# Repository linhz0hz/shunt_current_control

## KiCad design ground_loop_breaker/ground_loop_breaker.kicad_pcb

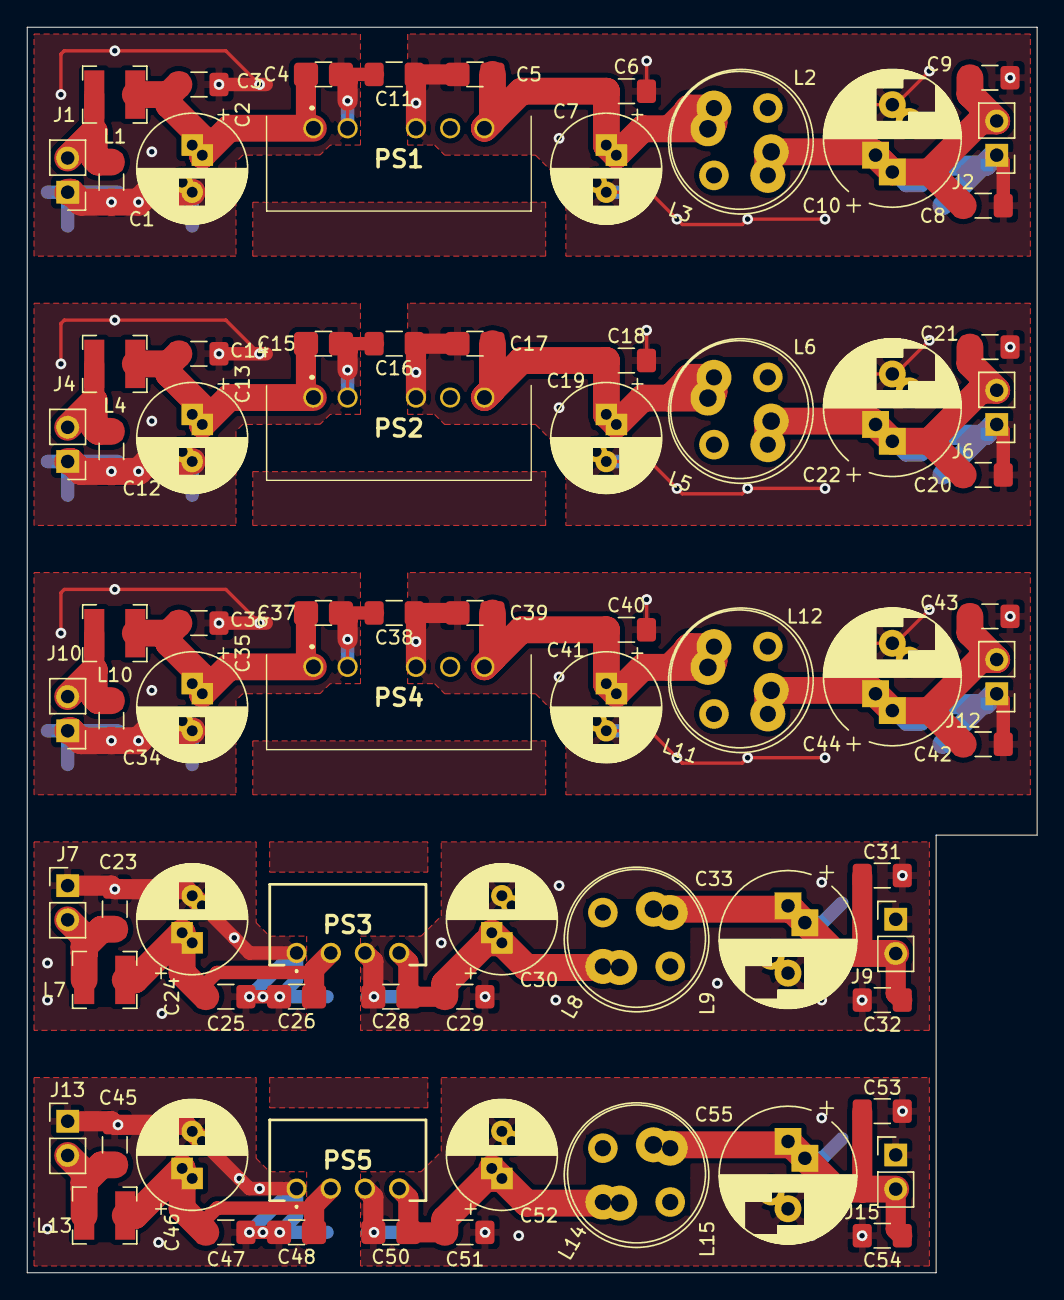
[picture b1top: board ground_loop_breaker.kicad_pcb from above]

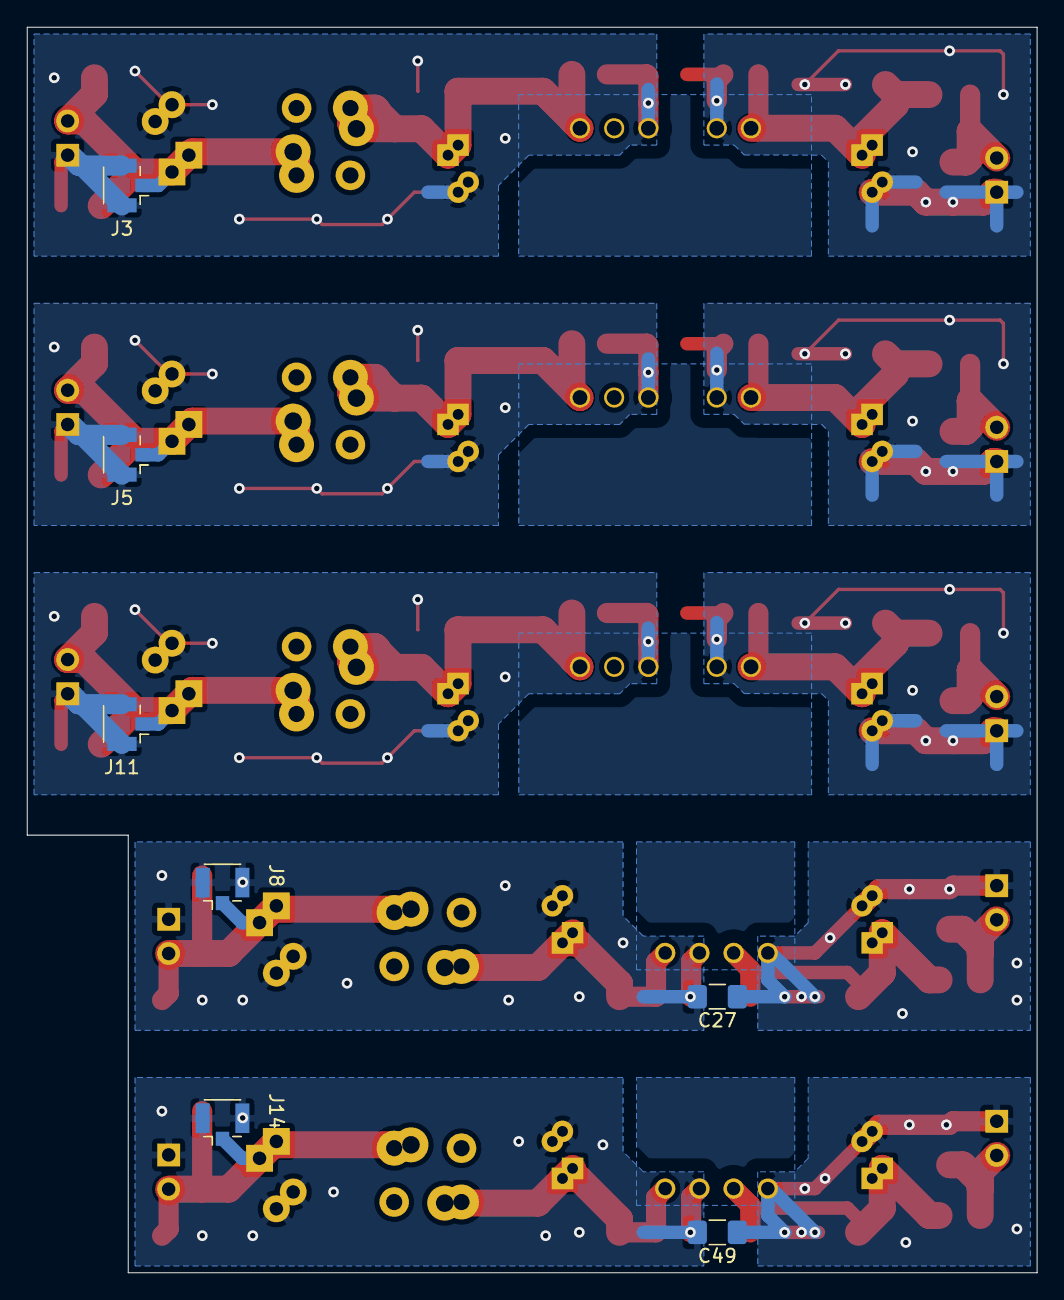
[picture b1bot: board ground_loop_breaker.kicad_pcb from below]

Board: 2 copper layers, 75.0 x 92.5 mm, 90 parts (7 on the bottom side), 30 nets.

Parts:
C1, C3, C6, C8, C9, C12, C14, C18, C20, C21, C23, C25, C29, C31, C32, C34, C36, C40, C42, C43, C45, C47, C51, C53, C54: C; C_1206_3216Metric_Pad1.42x1.75mm_HandSolder
C2, C7, C13, C19, C24, C30, C35, C41, C46, C52: CP; CP_Radial_D8_P3.5_2.5
C4, C5, C15, C17, C26, C28, C37, C39, C48, C50: C; C_1206_0805_dual
C10, C22, C33, C44, C55: CP; CP_Radial_D10.0mm_P3.5_5
C11, C16, C27, C38, C49: 270p 1kV; C_1206_3216Metric_Pad1.42x1.75mm_HandSolder
J1, J2, J4, J6, J7, J9, J10, J12, J13, J15: Conn_01x02_Male; PinHeader_1x02_P2.54mm_Vertical
J3, J5, J8, J11, J14: Conn_Coaxial; U.FL_Hirose_U.FL-R-SMT-1_Vertical
L1, L4, L7, L10, L13: L; L_Bourns-SRN4018
L2, L6, L9, L12, L15: 12RS105C; L_Radial_D10.5mm_P4.00x5.00mm_Murata_1200RS
L3, L5, L8, L11, L14: 12RS105C; L_Radial_D10.0mm_P5.00mm_Fastron_07P
PS1, PS2, PS4: PDM2-S5-S5-S; PDM2S5S5S
PS3, PS5: PDSE1-S5-S5-S; PDSE1S5S5S

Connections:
/power_module_A/VinN: C1.2, C2.2, C3.2, C4.2, C11.2, J1.1, PS1.2
/power_module_A/VinP: C1.1, J1.2, L1.1
/power_module_A/VoutN: C5.2, C6.2, C7.2, C8.2, C9.2, C10.2, C11.1, J2.1, J3.2, PS1.4
/power_module_A/VoutP: C8.1, C9.1, C10.1, J2.2, J3.1, L2.1, L3.1
/power_module_D/VinN: C23.2, C24.2, C25.2, C26.2, C27.2, J7.1, PS3.1
/power_module_D/VinP: C23.1, J7.2, L7.1
/power_module_D/VoutN: C27.1, C28.2, C29.2, C30.2, C31.2, C32.2, C33.2, J8.2, J9.1, PS3.3
/power_module_D/VoutP: C31.1, C32.1, C33.1, J8.1, J9.2, L8.1, L9.1
/sheet61365BC2/VinN: C45.2, C46.2, C47.2, C48.2, C49.2, J13.1, PS5.1
/sheet61365BC2/VinP: C45.1, J13.2, L13.1
/sheet61365BC2/VoutN: C49.1, C50.2, C51.2, C52.2, C53.2, C54.2, C55.2, J14.2, J15.1, PS5.3
/sheet61365BC2/VoutP: C53.1, C54.1, C55.1, J14.1, J15.2, L14.1, L15.1
/sheet613586DC/VinN: C12.2, C13.2, C14.2, C15.2, C16.2, J4.1, PS2.2
/sheet613586DC/VinP: C12.1, J4.2, L4.1
/sheet613586DC/VoutN: C16.1, C17.2, C18.2, C19.2, C20.2, C21.2, C22.2, J5.2, J6.1, PS2.4
/sheet613586DC/VoutP: C20.1, C21.1, C22.1, J5.1, J6.2, L5.1, L6.1
/sheet61358710/VinN: C34.2, C35.2, C36.2, C37.2, C38.2, J10.1, PS4.2
/sheet61358710/VinP: C34.1, J10.2, L10.1
/sheet61358710/VoutN: C38.1, C39.2, C40.2, C41.2, C42.2, C43.2, C44.2, J11.2, J12.1, PS4.4
/sheet61358710/VoutP: C42.1, C43.1, C44.1, J11.1, J12.2, L11.1, L12.1
unnamed: C2.1, C3.1, C4.1, L1.2, PS1.1
unnamed: C5.1, C6.1, C7.1, L2.2, L3.2, PS1.6
unnamed: C13.1, C14.1, C15.1, L4.2, PS2.1
unnamed: C17.1, C18.1, C19.1, L5.2, L6.2, PS2.6
unnamed: C24.1, C25.1, C26.1, L7.2, PS3.2
unnamed: C28.1, C29.1, C30.1, L8.2, L9.2, PS3.4
unnamed: C35.1, C36.1, C37.1, L10.2, PS4.1
unnamed: C39.1, C40.1, C41.1, L11.2, L12.2, PS4.6
unnamed: C46.1, C47.1, C48.1, L13.2, PS5.2
unnamed: C50.1, C51.1, C52.1, L14.2, L15.2, PS5.4

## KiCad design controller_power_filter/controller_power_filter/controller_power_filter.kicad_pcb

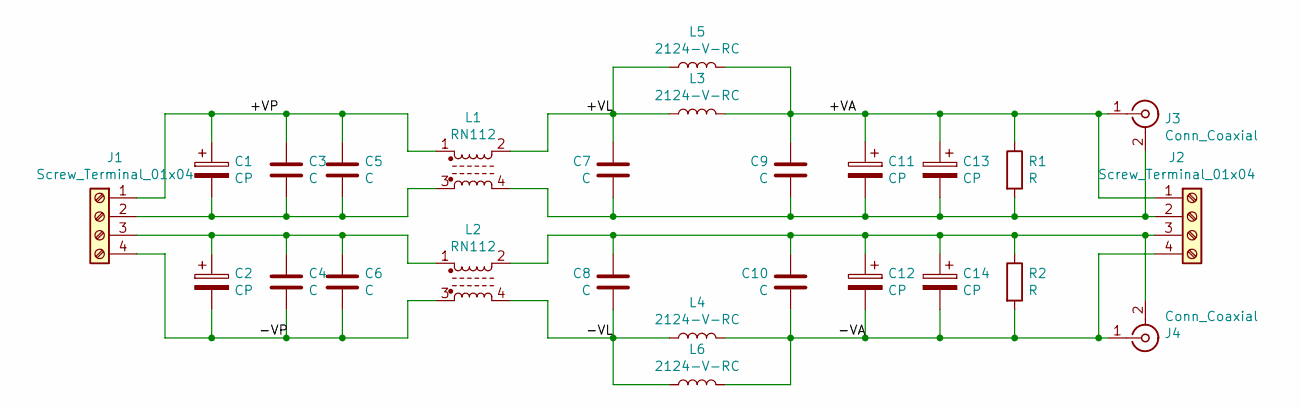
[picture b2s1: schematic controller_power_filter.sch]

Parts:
C1, C2, C11, C12, C13, C14: CP; CP_Radial_D10.0mm_P3.5_5
C3, C4, C5, C6, C7, C8, C9, C10: C; C_1206_0805_dual
J1, J2: Screw_Terminal_01x04; TerminalBlock_bornier-4_P5.08mm
J3, J4: Conn_Coaxial; U.FL_Hirose_U.FL-R-SMT-1_Vertical
L1, L2: RN112; Choke_Schaffner_RN102_112_204
L3, L4: 2124-V-RC; L_Toroid_Vertical_L21.6mm_W11.4mm_P7.62mm_Pulse_KM-3
L5, L6: 2124-V-RC; L_10.4x10.4_H4.8
R1, R2: R; R_1206_0805_dual

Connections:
/+VA: C9.1, C11.1, C13.1, J2.1, J3.1 (In), L3.2, L5.2, R1.1
/+VL: C7.1, L1.2, L3.1, L5.1
/+VP: C1.1, C3.1, C5.1, J1.1, L1.1
/-VA: C10.2, C12.2, C14.2, J2.4, J4.1 (In), L4.2, L6.2, R2.2
/-VL: C8.2, L2.4, L4.1, L6.1
/-VP: C2.2, C4.2, C6.2, J1.4, L2.3
unnamed: C1.2, C3.2, C5.2, J1.2, L1.3
unnamed: C2.1, C4.1, C6.1, J1.3, L2.1
unnamed: C8.1, C10.1, C12.1, C14.1, J2.3, J4.2 (Ext), L2.2, R2.1
unnamed: C7.2, C9.2, C11.2, C13.2, J2.2, J3.2 (Ext), L1.4, R1.2

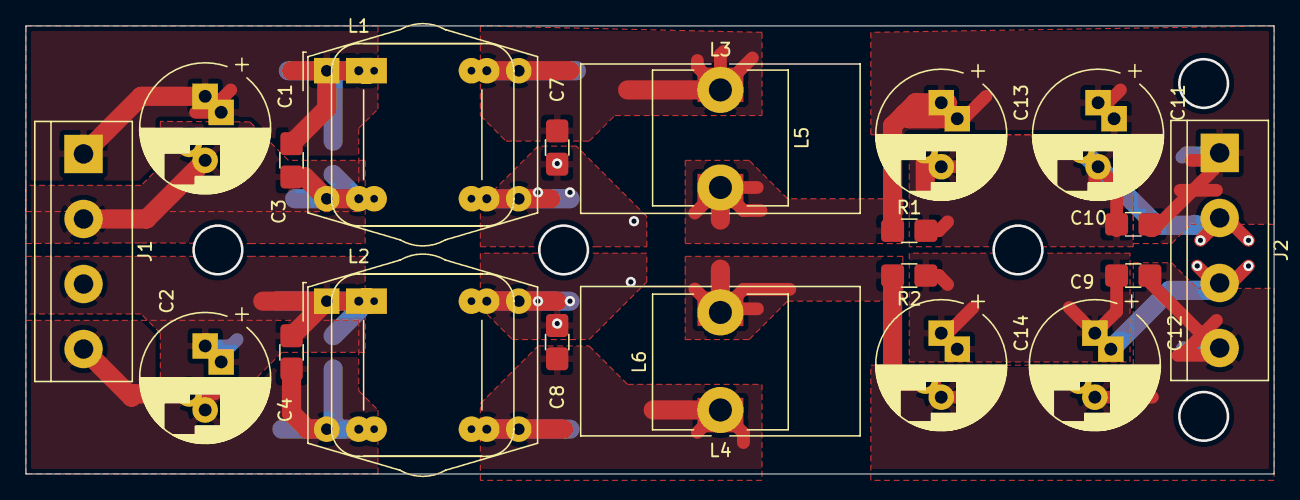
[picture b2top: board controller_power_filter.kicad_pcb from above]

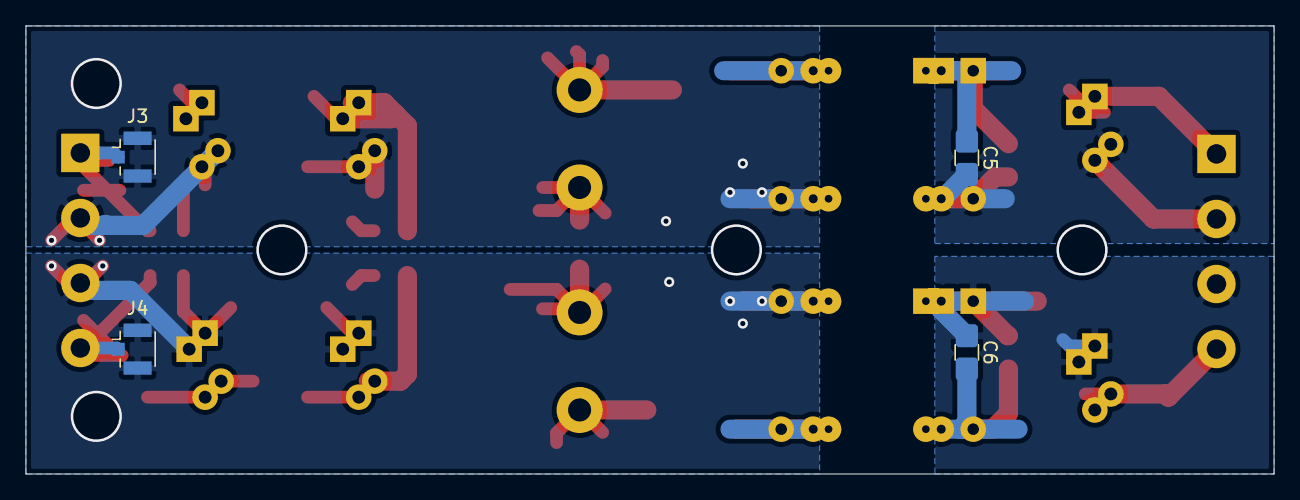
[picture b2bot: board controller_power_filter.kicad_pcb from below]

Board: 2 copper layers, 97.5 x 35.0 mm, 26 parts (4 on the bottom side), 10 nets.

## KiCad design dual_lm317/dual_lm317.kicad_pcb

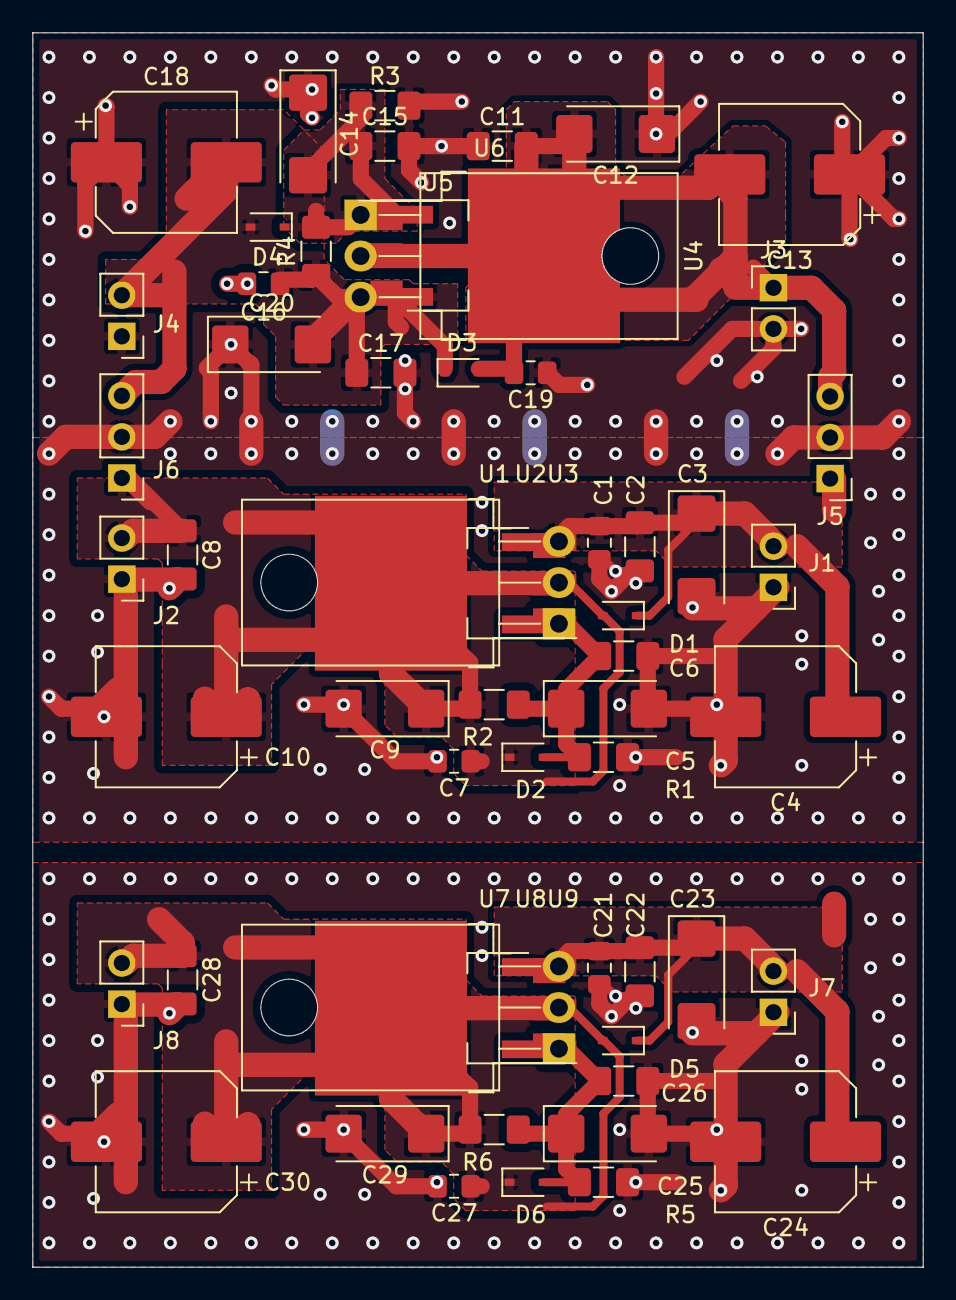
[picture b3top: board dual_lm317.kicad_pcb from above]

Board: 2 copper layers, 55.0 x 76.2 mm, 59 parts (0 on the bottom side), 11 nets.

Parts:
C1, C7, C16, C19, C21, C27: 0.1u; C_0805_2012Metric_Pad1.15x1.40mm_HandSolder
C2, C8, C11, C17, C22, C28: 1u; C_1206_3216Metric_Pad1.42x1.75mm_HandSolder
C3, C5, C9, C12, C14, C20, C23, C25, C29: Tant 10uF; CP_EIA-6032-15_Kemet-U_Pad2.25x2.35mm_HandSolder
C4, C10, C13, C18, C24, C30: Electrolytic; CP_Elec_8x10.5
C6, C15, C26: 0.01u c0g; C_1206_3216Metric_Pad1.42x1.75mm_HandSolder
D1, D2, D3, D4, D5, D6: D; D_SOD-323
J1, J2, J3, J4, J7, J8: Conn_01x02_Male; PinHeader_1x02_P2.54mm_Vertical
J5, J6: Conn_01x03_Male; PinHeader_1x03_P2.54mm_Vertical
R1, R2, R3, R4, R5, R6: R; R_1206_3216Metric_Pad1.42x1.75mm_HandSolder
U1, U7: LM317_3PinPackage; TO-220-3_Horizontal_TabDown
U2, U8: LT3080xST; SOT-223
U3, U9: LT3080xST; TO-263-3_TabPin4
U4: LM337_TO220; TO-220-3_Horizontal_TabDown
U5: LM337_SOT223; SOT-223-3_TabPin2
U6: LM337_TO263; TO-263-2

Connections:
/GNDA: C1.2, C2.2, C3.2, C4.2, C5.2, C6.2, C7.2, C8.2, C9.2, C10.2, C11.1, C12.1, C13.1, C14.1, C15.2, C16.2, C17.2, C18.1, C19.1, C20.1, J1.1, J2.1, J3.2, J4.1, J5.2, J6.2, R1.2, R3.2
/GNDB: C21.2, C22.2, C23.2, C24.2, C25.2, C26.2, C27.2, C28.2, C29.2, C30.2, J7.1, J8.1, R5.2
/VadjA: C5.1, C6.1, D2.2, R1.1, R2.2, U1.1, U2.1, U3.1
/VadjAN: C14.2, C15.1, D4.1, R3.1, R4.2, U4.1, U5.1, U6.1
/VadjB: C25.1, C26.1, D6.2, R5.1, R6.2, U7.1, U8.1, U9.1
/VinA: C1.1, C2.1, C3.1, C4.1, D1.1, J1.2, J5.1, U1.3, U2.3, U3.3
/VinAN: C11.2, C12.2, C13.2, C19.2, D3.2, J3.1, J5.3, U4.2, U5.2, U6.2
/VinB: C21.1, C22.1, C23.1, C24.1, D5.1, J7.2, U7.3, U8.3, U9.3
/VoutA: C7.1, C8.1, C9.1, C10.1, D1.2, D2.1, J2.2, J6.1, R2.1, U1.2, U2.2, U2.4, U3.2, U3.4
/VoutAN: C16.1, C17.1, C18.2, C20.2, D3.1, D4.2, J4.2, J6.3, R4.1, U4.3, U5.3, U6.3
/VoutB: C27.1, C28.1, C29.1, C30.1, D5.2, D6.1, J8.2, R6.1, U7.2, U8.2, U8.4, U9.2, U9.4

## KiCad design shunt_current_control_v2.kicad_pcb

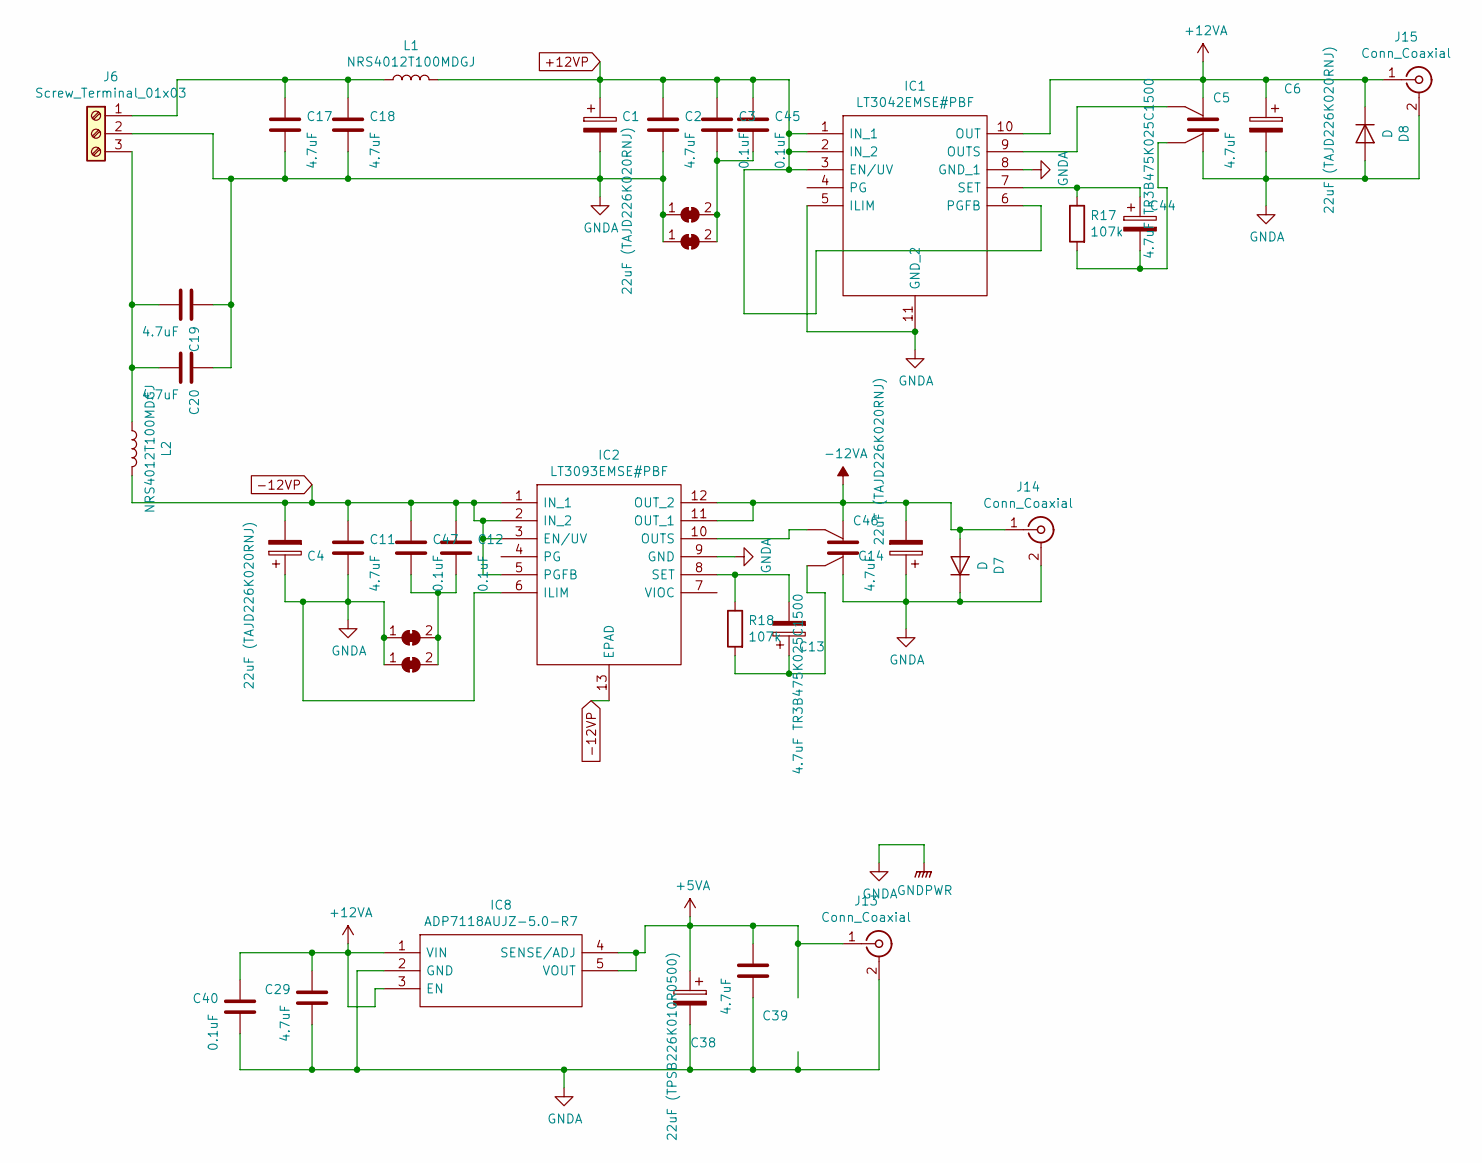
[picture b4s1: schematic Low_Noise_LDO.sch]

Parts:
C1, C4, C6, C14: 22uF (TAJD226K020RNJ); CP_EIA-7343-30_AVX-N_Pad2.25x2.55mm_HandSolder
C2, C11, C17, C18, C19, C20, C29, C39: 4.7uF; C_1206_3216Metric_Pad1.42x1.75mm_HandSolder
C3, C12, C40, C45, C47: 0.1uF; C_0805_2012Metric_Pad1.15x1.40mm_HandSolder
C5, C46: 4.7uF; C_1206_3216Metric_Pad1.42x1.75mm_Kelvin
C13, C44: 4.7uF TR3B475K025C1500; CP_EIA-3528-12_Kemet-T_Pad1.50x2.35mm_HandSolder
C38: 22uF (TPSB226K010R0500); CP_EIA-3528-15_AVX-H_Pad1.50x2.35mm_HandSolder
D7, D8: D; D_SOD-323_HandSoldering
IC1: LT3042EMSE#PBF; SOP50P490X110-11N; Mouser Part Number 584-LT3042EMSE#PBF
IC2: LT3093EMSE#PBF; SOP65P490X110-13N; Mouser Part Number 584-LT3093EMSE#PBF
IC8: ADP7118AUJZ-5.0-R7; SOT95P280X100-5N; Mouser Part Number 584-ADP7118AUJZ5.0R7
J6: Screw_Terminal_01x03; TerminalBlock_bornier-3_P5.08mm
J13, J14, J15: Conn_Coaxial; Coaxial_IPX_TE_23370191-1-2
JP5, JP6, JP7, JP8: SolderJumper_2_Bridged; DummyJumperStub
L1, L2: NRS4012T100MDGJ; L_Taiyo-Yuden_NR-40xx
R17, R18: 107k; R_0805_2012Metric_Pad1.15x1.40mm_HandSolder

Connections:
+5VA: C38.1, C39.1, IC8.4 (SENSE/ADJ), IC8.5 (VOUT), J13.1 (In); also elsewhere on the board
+12VA: C5.1, C6.1, C29.1, C40.1, D8.1 (K), IC1.10 (OUT), IC8.1 (VIN), IC8.3 (EN), J15.1 (In); also elsewhere on the board
+12VP: C1.1, C2.1, C3.1, C45.1, IC1.1 (IN_1), IC1.2 (IN_2), IC1.3 (EN/UV), IC1.6 (PGFB), L1.2; also elsewhere on the board
-12VA: C14.2, C46.1, D7.2 (A), IC2.11 (OUT_1), IC2.12 (OUT_2), J14.1 (In); also elsewhere on the board
-12VP: C4.2, C11.1, C12.1, C47.1, IC2.1 (IN_1), IC2.2 (IN_2), IC2.3 (EN/UV), IC2.5 (PGFB), IC2.13 (EPAD), L2.2
GNDA: C1.2, C2.2, C4.1, C5.2, C6.2, C11.2, C14.1, C17.2, C18.2, C19.1, C20.1, C29.2, C38.2, C39.2, C40.2, C46.2, D7.1 (K), D8.2 (A), IC1.5 (ILIM), IC1.8 (GND_1), IC1.11 (GND_2), IC2.6 (ILIM), IC2.9 (GND), IC8.2 (GND), J6.2, J13.2 (Ext), J14.2 (Ext), J15.2 (Ext), JP5.1 (A), JP6.1 (A), JP7.1 (A), JP8.1 (A); also elsewhere on the board
unnamed: C3.2, C45.2, JP5.2 (B), JP6.2 (B)
unnamed: C5.3, IC1.9 (OUTS)
unnamed: C12.2, C47.2, JP7.2 (B), JP8.2 (B)
unnamed: C13.1, C46.4, R18.2
unnamed: C13.2, IC2.8 (SET), R18.1
unnamed: C17.1, C18.1, J6.1, L1.1
unnamed: C19.2, C20.2, J6.3, L2.1
unnamed: C44.1, IC1.7 (SET), R17.1
unnamed: C5.4, C44.2, R17.2
unnamed: C46.3, IC2.10 (OUTS)

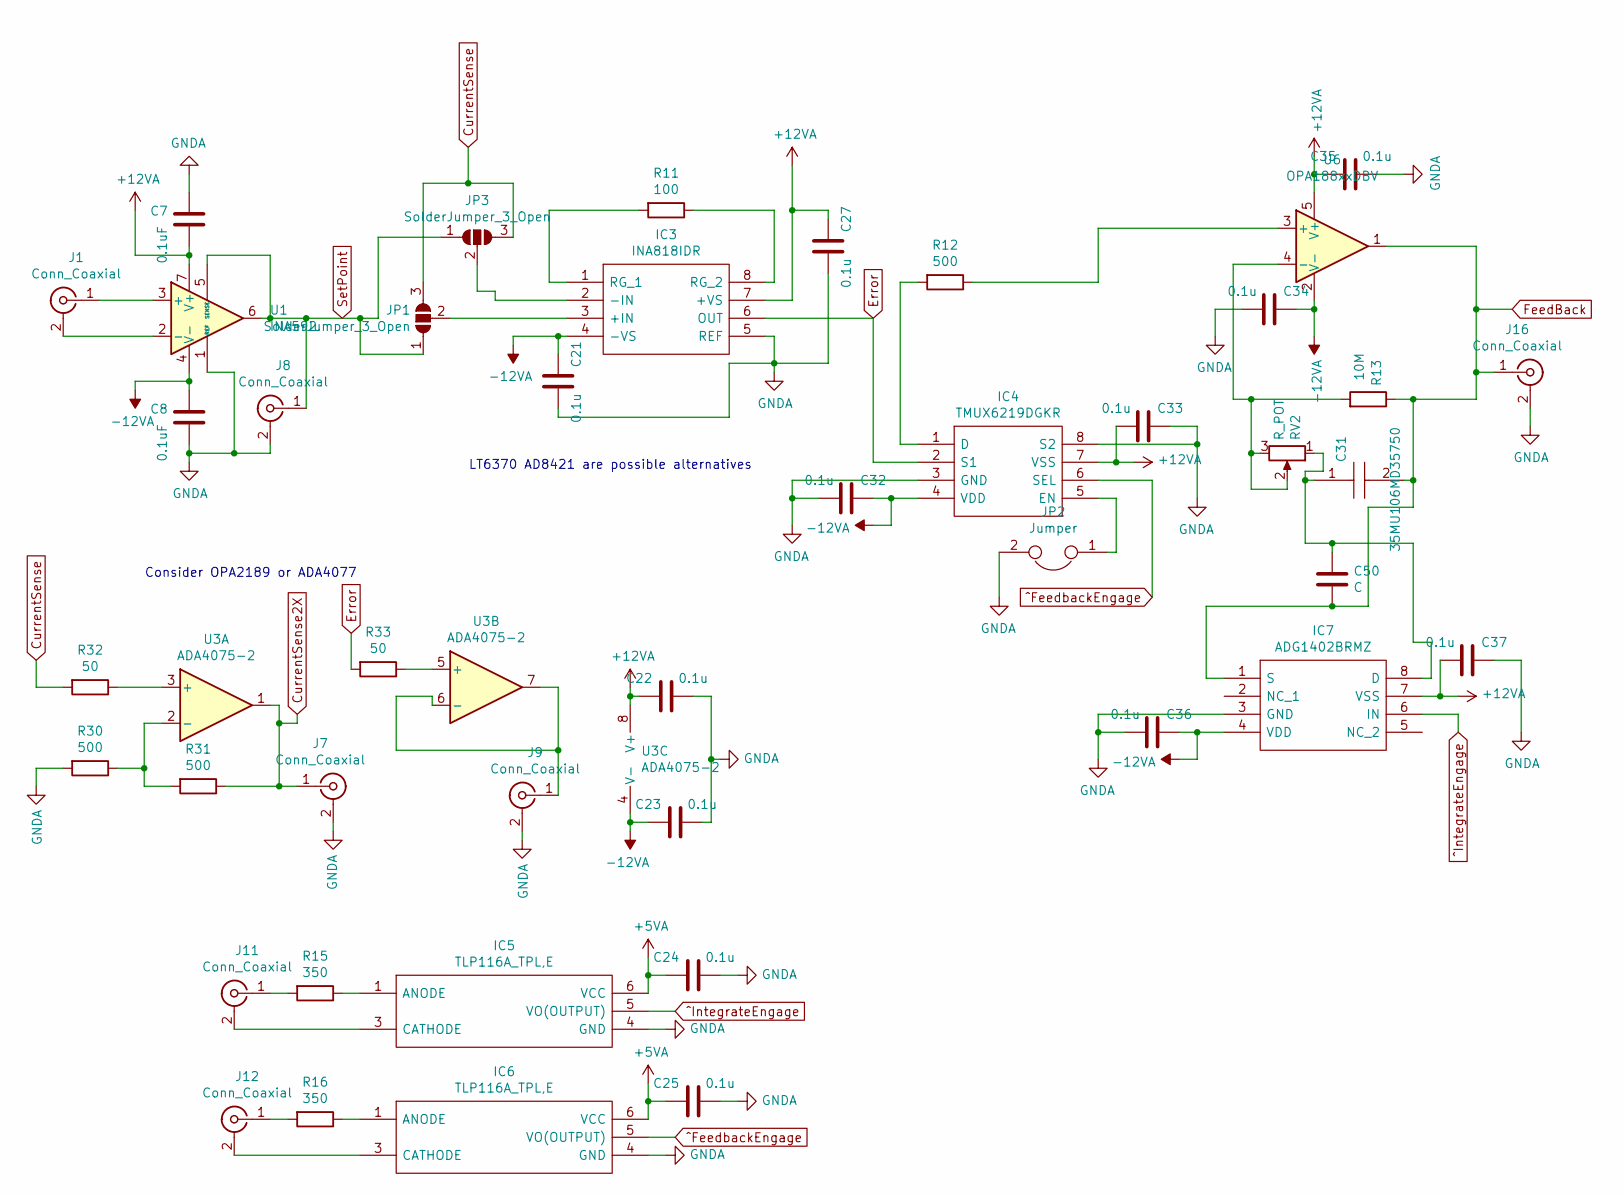
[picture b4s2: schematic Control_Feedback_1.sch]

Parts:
C7, C8: 0.1uF; C_0805_2012Metric_Pad1.15x1.40mm_HandSolder
C21, C22, C23, C24, C25, C27, C32, C33, C34, C35, C36, C37: 0.1u; C_0805_2012Metric_Pad1.15x1.40mm_HandSolder
C31: 35MU106MD35750; CAPC5750X280N; Mouser Part Number 232-35MU106MD35750
C50: C; C_Radial_D8.0mm_H7.0mm_P3.50mm
IC3: INA818IDR; SOIC-8_3.9x4.9mm_P1.27mm; Mouser Part Number 595-INA818IDR
IC4: TMUX6219DGKR; SOP65P490X110-8N; Mouser Part Number 595-TMUX6219DGKR
IC5, IC6: TLP116A_TPL,E; SOT127P700X230-5N; Mouser Part Number 757-TLP116A(TPLE
IC7: ADG1402BRMZ; SOP65P490X110-8N; Mouser Part Number 584-ADG1402BRMZ
J1: Conn_Coaxial; SMA_Amphenol_132134-10_Vertical
J7, J8, J9, J11, J12, J16: Conn_Coaxial; Coaxial_IPX_TE_23370191-1-2
JP1, JP3: SolderJumper_3_Open; SolderJumper-3_P1.3mm_Open_RoundedPad1.0x1.5mm
JP2: Jumper; SolderJumper-2_P1.3mm_Open_RoundedPad1.0x1.5mm
R11: 100; R_1206_3216Metric_Pad1.42x1.75mm_HandSolder
R12: 500; R_1206_3216Metric_Pad1.42x1.75mm_HandSolder
R13: 10M; R_1206_3216Metric_Pad1.42x1.75mm_HandSolder
R15, R16: 350; R_0805_2012Metric_Pad1.15x1.40mm_HandSolder
R30, R31: 500; R_1206_0805_dual
R32, R33: 50; R_0805_2012Metric_Pad1.15x1.40mm_HandSolder
RV2: R_POT; 3361P1253GLF
U1: INA592; SOIC-8_3.9x4.9mm_P1.27mm
U3: ADA4075-2; SOIC-8_3.9x4.9mm_P1.27mm
U6: OPA188xxDBV; TSOT-23-5

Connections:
+5VA: C24.2, C25.2, IC5.6 (VCC), IC6.6 (VCC); also elsewhere on the board
+12VA: C7.2, C22.2, C27.2, C33.1, C35.2, C37.1, IC3.7 (+VS), IC4.7 (VSS), IC7.7 (VSS), U1.7 (V+), U3.8 (V+), U6.5 (V+); also elsewhere on the board
-12VA: C8.1, C21.2, C23.2, C32.2, C34.2, C36.2, IC3.4 (-VS), IC4.4 (VDD), IC7.4 (VDD), U1.4 (V-), U3.4 (V-), U6.2 (V-); also elsewhere on the board
CurrentSense: JP1.3 (B), JP3.3 (B), R32.2; also elsewhere on the board
CurrentSense2X: J7.1 (In), R31.1, U3.1
Error: IC3.6 (OUT), IC4.2 (S1), R33.2
FeedBack: C31.2, C50.1, IC7.1 (S), J16.1 (In), R13.1, U6.1; also elsewhere on the board
GNDA: C7.1, C8.2, C21.1, C22.1, C23.1, C24.1, C25.1, C27.1, C32.1, C33.2, C34.1, C35.1, C36.1, C37.2, IC3.5 (REF), IC4.3 (GND), IC4.8 (S2), IC5.4 (GND), IC6.4 (GND), IC7.3 (GND), J7.2 (Ext), J8.2 (Ext), J9.2 (Ext), J16.2 (Ext), JP2.2, R30.2, U1.1 (REF); also elsewhere on the board
unnamed: C31.1, C50.2, IC7.8 (D), RV2.1
unnamed: IC3.1 (RG_1), R11.2
unnamed: IC3.2 (-IN), JP3.2 (C)
unnamed: IC3.3 (+IN), JP1.2 (C)
unnamed: IC3.8 (RG_2), R11.1
unnamed: IC4.1 (D), R12.2
unnamed: IC4.5 (EN), JP2.1
unnamed: IC5.1 (ANODE), R15.1
unnamed: IC5.3 (CATHODE), J11.2 (Ext)
unnamed: IC6.1 (ANODE), R16.1
unnamed: IC6.3 (CATHODE), J12.2 (Ext)
unnamed: J1.1 (In), U1.3 (+)
unnamed: J1.2 (Ext), U1.2 (-)
unnamed: J9.1 (In), U3.6 (-), U3.7
unnamed: J11.1 (In), R15.2
unnamed: J12.1 (In), R16.2
unnamed: R12.1, U6.3 (+)
unnamed: R13.2, RV2.2, RV2.3, U6.4 (-)
unnamed: R30.1, R31.2, U3.2 (-)
unnamed: R32.1, U3.3 (+)
unnamed: R33.1, U3.5 (+)
SetPoint: J8.1 (In), JP1.1 (A), JP3.1 (A), U1.5 (SENSE), U1.6
^FeedbackEngage: IC4.6 (SEL), IC6.5 (VO(OUTPUT))
^IntegrateEngage: IC5.5 (VO(OUTPUT)), IC7.6 (IN)

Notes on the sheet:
Consider OPA2189 or ADA4077
LT6370 AD8421 are possible alternatives

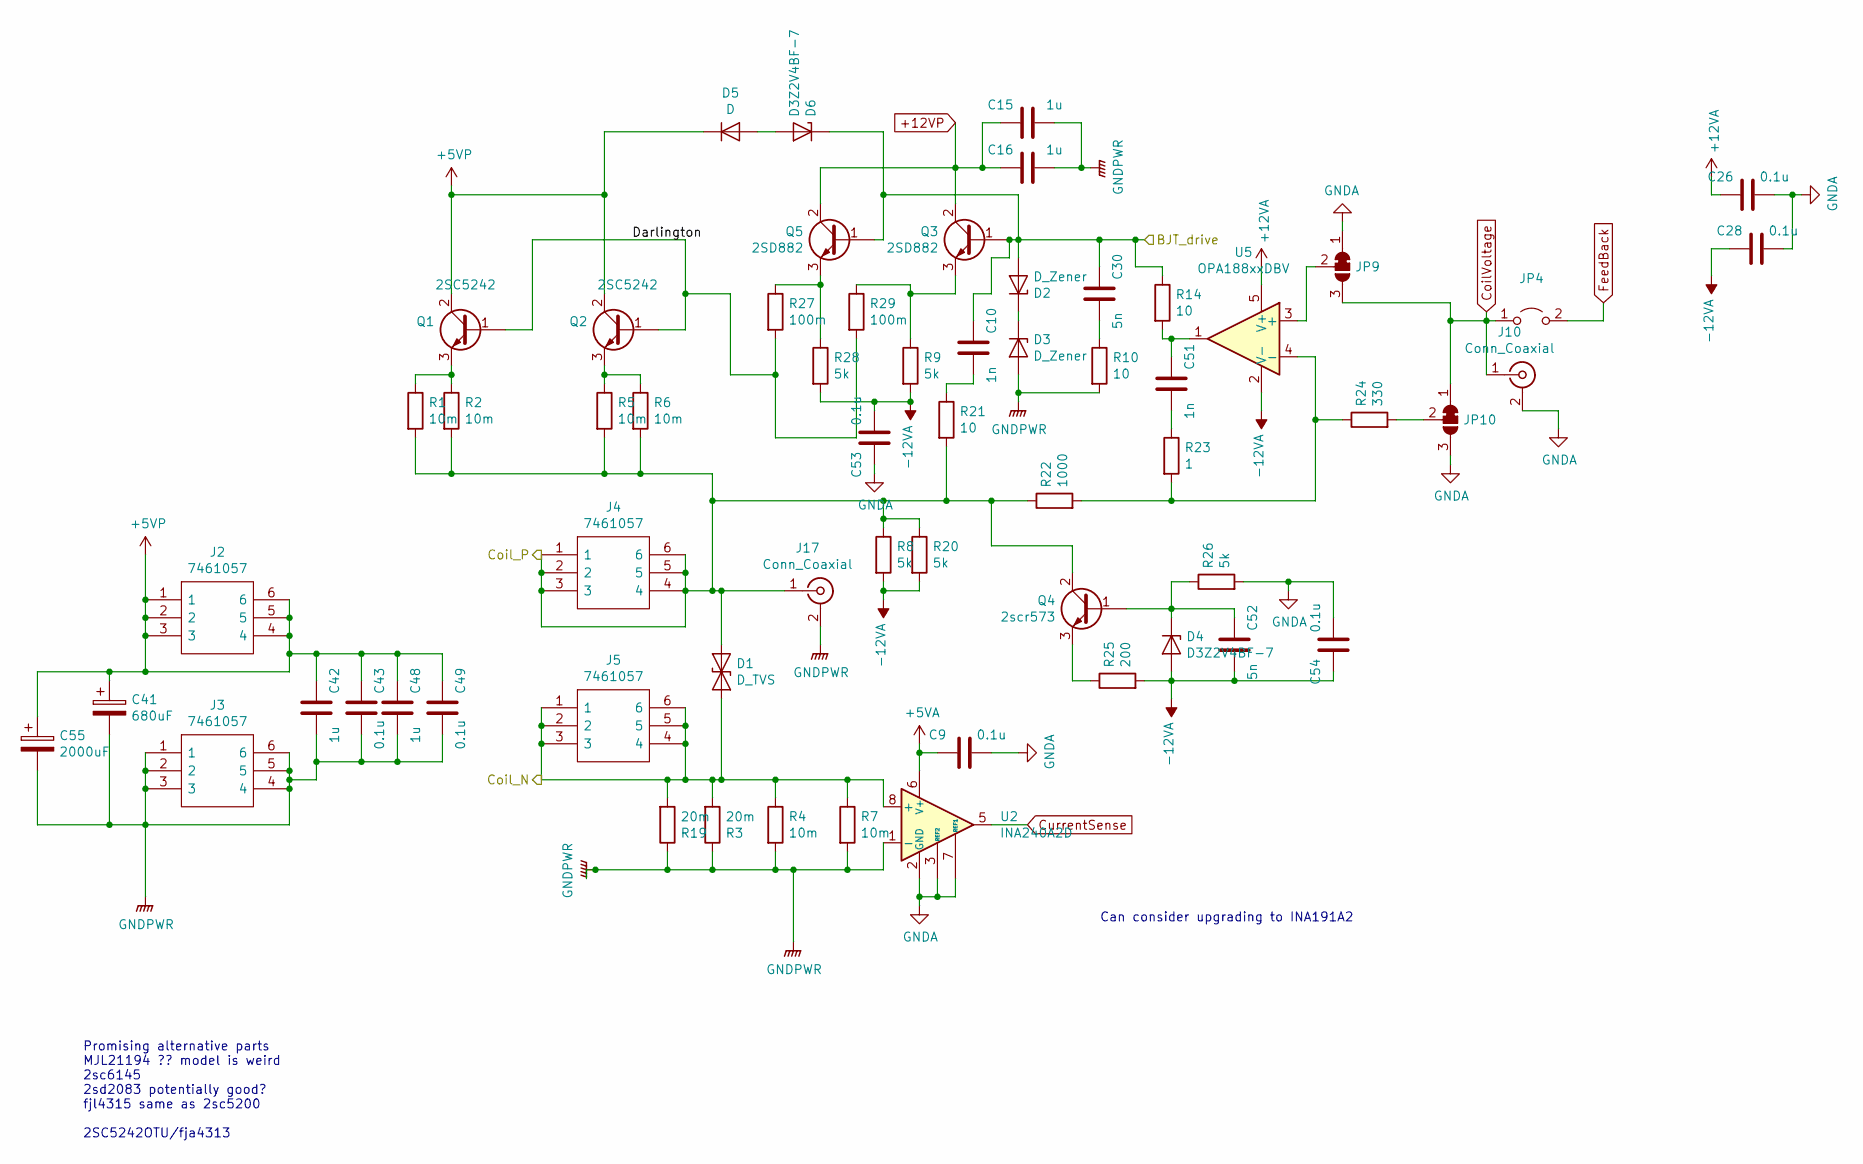
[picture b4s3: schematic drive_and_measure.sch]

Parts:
C9, C26, C28, C43, C49, C53, C54: 0.1u; C_0805_2012Metric_Pad1.15x1.40mm_HandSolder
C10, C51: 1n; C_1206_3216Metric
C15: 1u; C_1206_3216Metric_Pad1.42x1.75mm_HandSolder
C16, C42, C48: 1u; C_1206_3216Metric
C30, C52: 5n; C_1206_3216Metric
C41: 680uF; CP_Radial_D10.0mm_P3.5_5
C55: 2000uF; CP_Radial_D10.0mm_P5.00mm
D1: D_TVS; D_SMB-SMC_Universal_Handsoldering
D2, D3: D_Zener; D_SOD-323_HandSoldering
D4, D6: D3Z2V4BF-7; D_SOD-323_HandSoldering
D5: D; D_SOD-323_HandSoldering
J2, J3, J4, J5: 7461057; Mouser Part Number 710-7461057
J10, J17: Conn_Coaxial; Coaxial_IPX_TE_23370191-1-2
JP4: Jumper_2_Open; SolderJumper-2_P1.3mm_Open_RoundedPad1.0x1.5mm
JP9, JP10: SolderJumper_3_Bridged12; SolderJumper-3_P1.3mm_Bridged12_RoundedPad1.0x1.5mm
Q1, Q2: 2SC5242; TO-3P-3_Vertical
Q3, Q5: 2SD882; TO-126-3_Horizontal_TabDown
Q4: 2scr573; TO-252-2
R1, R2, R5, R6: 10m; R_1206_3216Metric_Pad1.42x1.75mm_HandSolder
R3: 20m; R_2512_6332Metric_Pad1.52x3.35mm_HandSolder
R4, R7: 10m; Y14730R00500B0R
R8, R9, R20, R26, R28: 5k; R_1206_3216Metric_Pad1.42x1.75mm_HandSolder
R10, R14, R21: 10; R_1206_3216Metric_Pad1.42x1.75mm_HandSolder
R19: 20m; R_CSSH2728_handsolder
R22: 1000; R_1206_3216Metric_Pad1.42x1.75mm_HandSolder
R23: 1; R_1206_3216Metric_Pad1.42x1.75mm_HandSolder
R24: 330; R_1206_3216Metric_Pad1.42x1.75mm_HandSolder
R25: 200; R_1206_3216Metric_Pad1.42x1.75mm_HandSolder
R27, R29: 100m; R_1206_3216Metric_Pad1.42x1.75mm_HandSolder
U2: INA240A2D; SOIC-8_3.9x4.9mm_P1.27mm
U5: OPA188xxDBV; TSOT-23-5

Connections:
+5VA: C9.2, U2.6 (V+); also elsewhere on the board
+5VP: C41.1, C42.2, C43.2, C48.2, C49.2, C55.1, D5.1 (K), J2.1, J2.2, J2.3, J2.4, J2.5, J2.6, Q1.2 (C), Q2.2 (C)
+12VA: C26.2, U5.5 (V+); also elsewhere on the board
+12VP: C15.2, C16.2, Q3.2 (C), Q5.2 (C); also elsewhere on the board
-12VA: C28.2, C52.1, C53.1, C54.2, D4.2 (A), R8.2, R9.2, R20.2, R25.2, R28.2, U5.2 (V-); also elsewhere on the board
/drive_and_measure/BJT_drive: C10.2, C30.2, D2.2 (A), D6.1 (K), Q3.1 (B), Q5.1 (B), R14.1
/drive_and_measure/Coil_N: D1.2 (A2), J5.1, J5.2, J5.3, J5.4, J5.5, J5.6, R3.2, R4.1, R7.1, R19.2, U2.8 (+)
/drive_and_measure/Coil_P: D1.1 (A1), J4.1, J4.2, J4.3, J4.4, J4.5, J4.6, J17.1 (In), Q4.2 (C), R1.2, R2.2, R5.2, R6.2, R8.1, R20.1, R21.2, R22.1
/drive_and_measure/Darlington: Q1.1 (B), Q2.1 (B), R27.2, R29.2
CoilVoltage: J10.1 (In), JP4.1 (A), JP9.3 (B), JP10.1 (A)
CurrentSense: U2.5; also elsewhere on the board
FeedBack: JP4.2 (B); also elsewhere on the board
GNDA: C9.1, C15.1, C16.1, C26.1, C28.1, C41.2, C42.1, C43.1, C48.1, C49.1, C53.2, C54.1, C55.2, D3.2 (A), J3.1, J3.2, J3.3, J3.4, J3.5, J3.6, J10.2 (Ext), J17.2 (Ext), JP9.1 (A), JP10.3 (B), R3.1, R4.2, R7.2, R10.2, R19.1, R26.2, U2.1 (-), U2.2 (GND), U2.3 (REF2), U2.4 (GND), U2.7 (REF1); also elsewhere on the board
unnamed: C10.1, R21.1
unnamed: C30.1, R10.1
unnamed: C51.1, R23.1
unnamed: C51.2, R14.2, U5.1
unnamed: C52.2, D4.1 (K), Q4.1 (B), R26.1
unnamed: D2.1 (K), D3.1 (K)
unnamed: D5.2 (A), D6.2 (A)
unnamed: JP9.2 (C), U5.3 (+)
unnamed: JP10.2 (C), R24.2
unnamed: Q1.3 (E), R1.1, R2.1
unnamed: Q2.3 (E), R5.1, R6.1
unnamed: Q3.3 (E), R9.1, R29.1
unnamed: Q4.3 (E), R25.1
unnamed: Q5.3 (E), R27.1, R28.1
unnamed: R22.2, R23.2, R24.1, U5.4 (-)

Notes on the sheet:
Promising alternative parts MJL21194 ?? model is weird 2sc6145 2sd2083 potentially good? fjl4315 same as 2sc5200 2SC5242OTU/fja4313
Can consider upgrading to INA191A2
